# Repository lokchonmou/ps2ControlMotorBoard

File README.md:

# ps2ControlMotorBoard
A simple 3 small DC brushed motor wireless controller with PS2 handle

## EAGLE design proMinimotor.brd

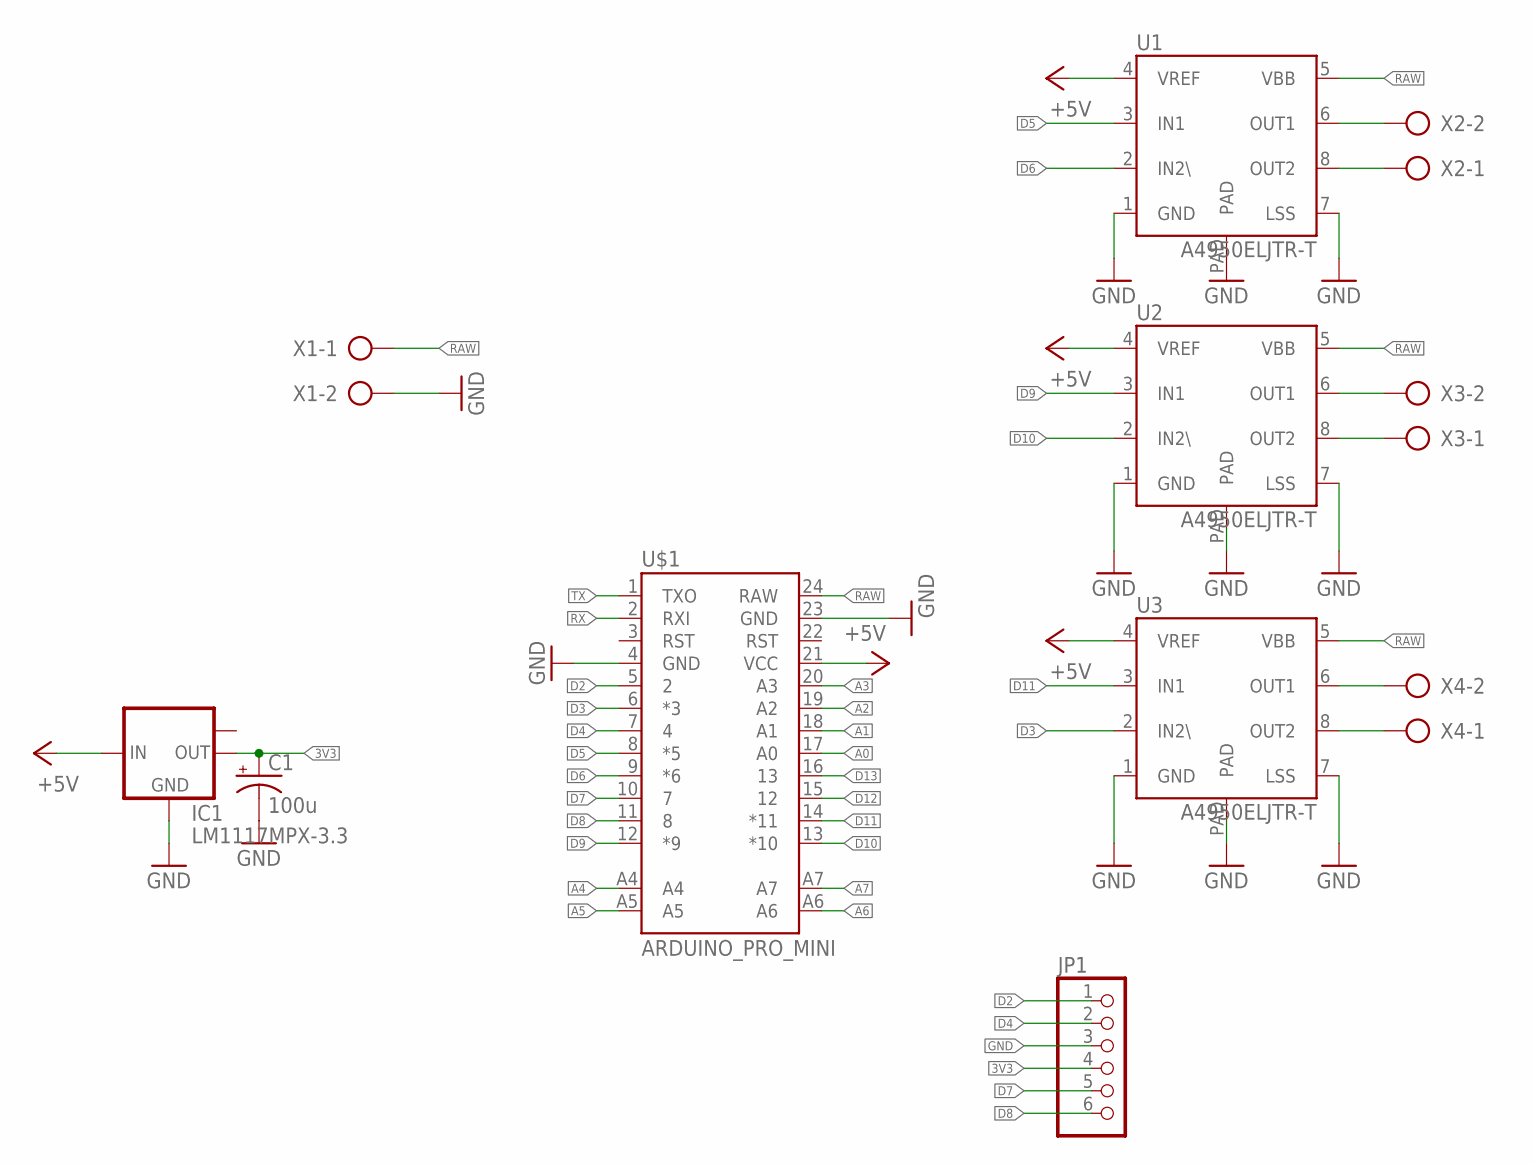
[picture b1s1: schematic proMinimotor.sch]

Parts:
C1: 100u; E2,5-7
IC1: LM1117MPX-3.3; SOT223
JP1: PINHD-1X6/90; 1X06/90
U1, U2, U3: A4950ELJTR-T; SOIC8TP
U$1: ARDUINO_PRO_MINI
X1, X2, X3, X4: AK500/2

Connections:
3V3: C1.+, IC1.2 (OUT), JP1.4
+5V: IC1.3 (IN), U1.4 (VREF), U2.4 (VREF), U3.4 (VREF), U$1.21 (VCC)
A0: U$1.17 (A0)
A1: U$1.18 (A1)
A2: U$1.19 (A2)
A3: U$1.20 (A3)
A4: U$1.A4
A5: U$1.A5
A6: U$1.A6
A7: U$1.A7
D2: JP1.1, U$1.5 (2)
D3: U3.2 (IN2\), U$1.6 (*3)
D4: JP1.2, U$1.7 (4)
D5: U1.3 (IN1), U$1.8 (*5)
D6: U1.2 (IN2\), U$1.9 (*6)
D7: JP1.5, U$1.10 (7)
D8: JP1.6, U$1.11 (8)
D9: U2.3 (IN1), U$1.12 (*9)
D10: U2.2 (IN2\), U$1.13 (*10)
D11: U3.3 (IN1), U$1.14 (*11)
D12: U$1.15 (12)
D13: U$1.16 (13)
GND: C1.-, IC1.1 (GND), JP1.3, U1.1 (GND), U1.7 (LSS), U1.PAD, U2.1 (GND), U2.7 (LSS), U2.PAD, U3.1 (GND), U3.7 (LSS), U3.PAD, U$1.4 (GND), U$1.23 (GND), X1.2
unnamed: U1.8 (OUT2), X2.1
unnamed: U1.6 (OUT1), X2.2
unnamed: U2.8 (OUT2), X3.1
unnamed: U2.6 (OUT1), X3.2
unnamed: U3.8 (OUT2), X4.1
unnamed: U3.6 (OUT1), X4.2
RAW: U1.5 (VBB), U2.5 (VBB), U3.5 (VBB), U$1.24 (RAW), X1.1
RX: U$1.2 (RXI)
TX: U$1.1 (TXO)

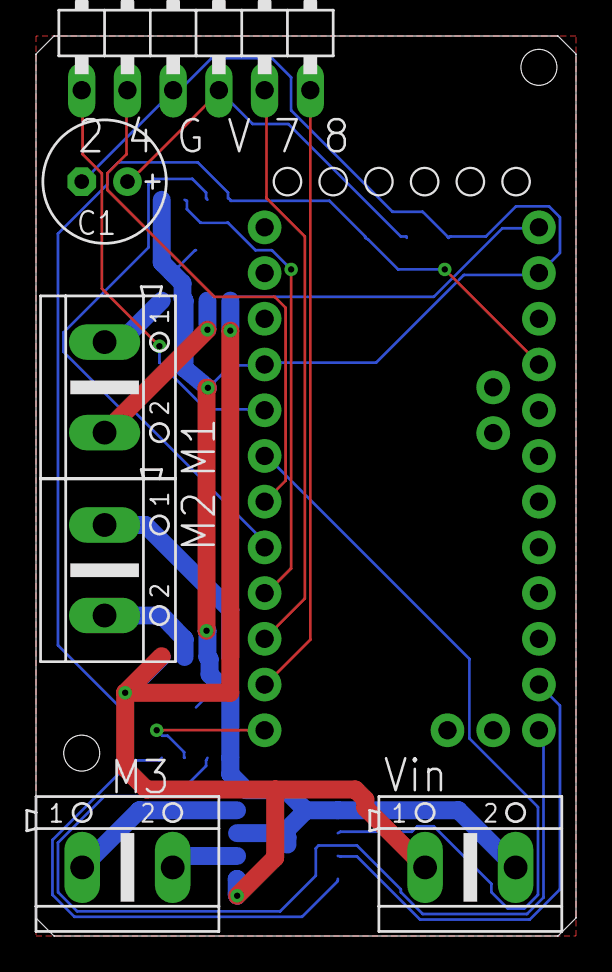
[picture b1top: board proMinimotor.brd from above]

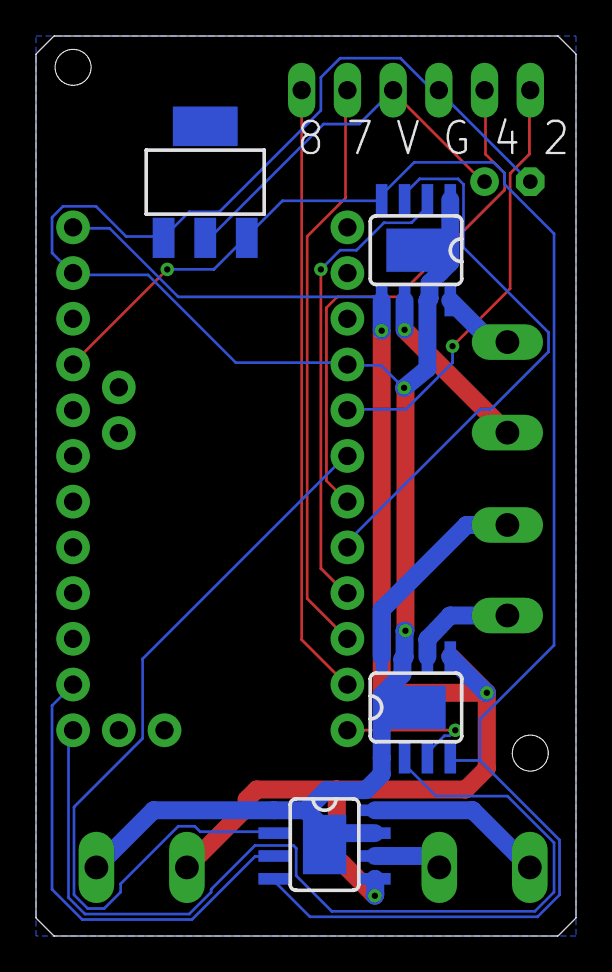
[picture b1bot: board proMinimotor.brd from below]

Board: 2 copper layers, 30.0 x 50.0 mm, 11 parts (4 on the bottom side), 20 nets.

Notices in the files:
parts and their libraries:
SparkFun-Boards: Licensing: Creative Commons ShareAlike 4.0 International - https://creativecommons.org/licenses/by-sa/4.0
